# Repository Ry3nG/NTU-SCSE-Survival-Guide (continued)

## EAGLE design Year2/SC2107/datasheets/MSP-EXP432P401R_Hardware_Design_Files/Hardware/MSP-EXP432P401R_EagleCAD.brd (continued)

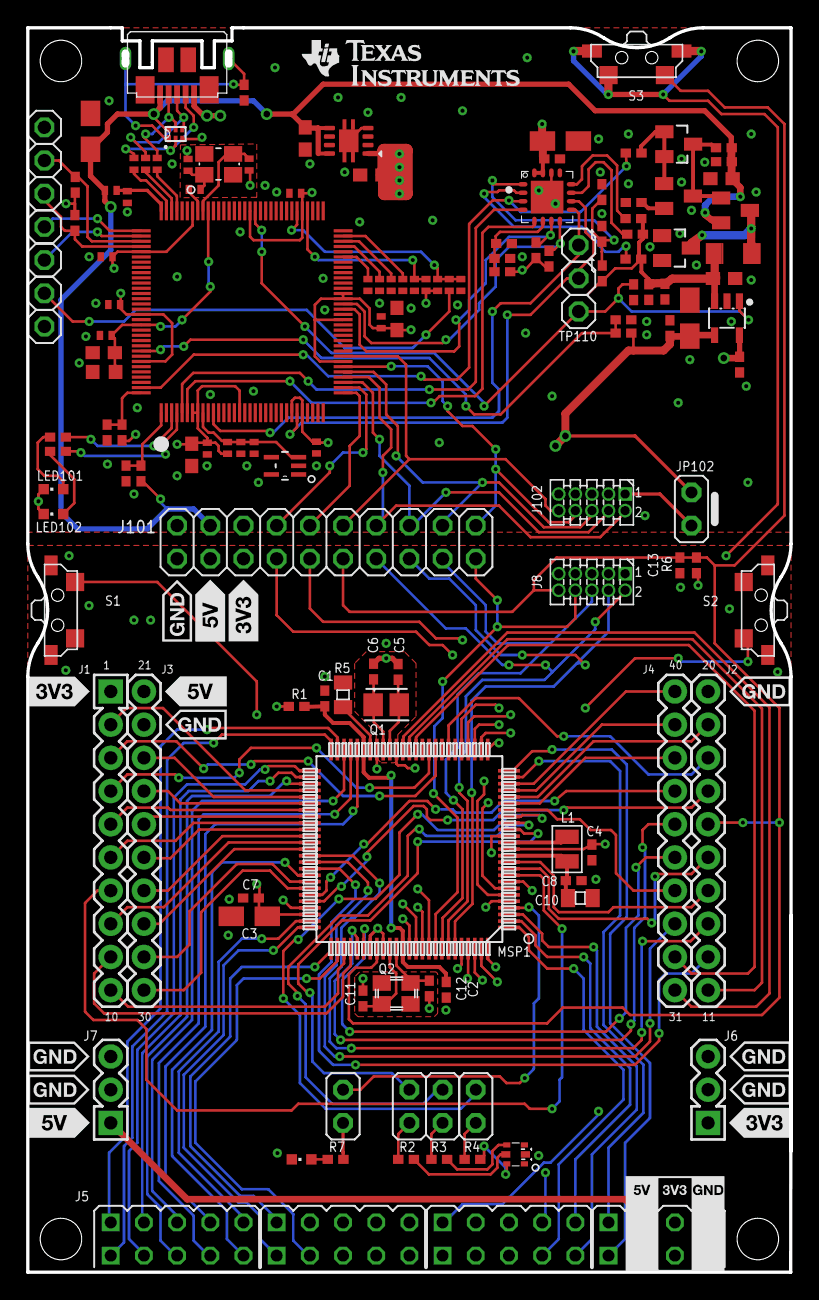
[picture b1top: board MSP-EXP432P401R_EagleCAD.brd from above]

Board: 4 copper layers, 58.1 x 94.9 mm, 149 parts (0 on the bottom side), 160 nets.

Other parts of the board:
DRAW3: LOGO-ROCKET-10X7MM-BRD
U$4: LOGO16_TPLACE

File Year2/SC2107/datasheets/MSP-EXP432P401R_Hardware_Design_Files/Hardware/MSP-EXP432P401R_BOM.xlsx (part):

BOM for MSP-EXP432P401R
Do not populate (Dnp) part if Quantity equals zero
Use exact PartNumber and Manufacturer if this data is provided
Feedback from CM needed where supplier equals CM
 | Qty | Reference | Manufacturer | Description | Part Number | PCB Decal/Package | Value | Supplier1 | Supplier Part Number | Comment
 | 1 | C1 | Standard | CAP CER 0.1UF 10V 20% X5R 0402,Digikey 445-4984-1-ND |  | 402 | 100n | Digikey | 445-4984-1-ND
 | 1 | C2 | Standard | CAP CER 0.1UF 10V 20% X5R 0402,Digikey 445-4984-1-ND |  | 402 | 100n | Digikey | 445-4984-1-ND
 | 1 | C3 | Standard | CAP TANT 10UF 10V 20% 1206,Digikey 493-2351-1-ND |  | TANT_3216 | 10u | Digikey | 493-2351-1-ND
 | 1 | C4 | Standard | CAP CER 0.1UF 10V 20% X5R 0402,Digikey 445-4984-1-ND |  | 402 | 100n | Digikey | 445-4984-1-ND
 | 1 | C5 | Standard | CAP CER 22PF 50V 5% NP0 0402, Digikey 445-1239-1-ND |  | 402 | 22p | Digikey | 445-1239-1-ND
 | 1 | C6 | Standard | CAP CER 22PF 50V 5% NP0 0402, Digikey 445-1239-1-ND |  | 402 | 22p | Digikey | 445-1239-1-ND
 | 1 | C7 | Standard | CAP CER 0.1UF 10V 20% X5R 0402,Digikey 445-4984-1-ND |  | 402 | 100n | Digikey | 445-4984-1-ND
 | 1 | C8 | Standard | CAP CER 0.1UF 10V 20% X5R 0402,Digikey 445-4984-1-ND |  | 402 | 100n | Digikey | 445-4984-1-ND
 | 1 | C10 | Standard | CAP CER 4.7UF 10V Y5V 0805, Digikey 445-1370-1-ND |  | 805 | 4.7u | Digikey | 445-1370-1-ND
 | 1 | C11 | Standard | CAP CER 22PF 50V 5% NP0 0402, Digikey 445-1239-1-ND |  | 402 | 22p | Digikey | 445-1239-1-ND
 | 1 | C12 | Standard | CAP CER 22PF 50V 5% NP0 0402, Digikey 445-1239-1-ND |  | 402 | 22p | Digikey | 445-1239-1-ND
 | 1 | C13 | Standard | CAP CER 1000PF 50V 10% X7R 0402,Digikey 445-1256-1-ND |  | 402 | 1n | Digikey | 445-1256-1-ND
 | 1 | C101 | Standard | CAP CER 12PF 50V 5% NP0 0402,Digikey 445-1236-1-ND |  | 402 | 12p | Digikey | 445-1236-1-ND
 | 1 | C102 | Standard | CAP CER 12PF 50V 5% NP0 0402,Digikey 445-1236-1-ND |  | 402 | 12p | Digikey | 445-1236-1-ND
 | 1 | C103 | Standard | CAP CER 0.1UF 10V 20% X5R 0402,Digikey 445-4984-1-ND |  | 402 | 100n | Digikey | 445-4984-1-ND
 | 1 | C104 | Standard | CAP CER 10000PF 10V 10% X7R 0402, Digikey 478-7890-1-ND |  | 402 | 10n | Digikey | 478-7890-1-ND
 | 1 | C105 | Standard | CAP CER 2.2UF 10V 10% X5R 0603, Digikey 587-1253-1-ND |  | 603 | 2.2u | Digikey | 587-1253-1-ND
 | 1 | C106 | Standard | CAP TANT 4.7UF 10V 10% 1206,Digikey 478-8221-1-ND |  | TANT_3216 | 4.7u | Digikey | 478-8221-1-ND
 | 1 | C107 | Standard | CAP CER 1UF 10V 10% X5R 0603, Digikey 445-1321-1-ND |  | 603 | 1u | Digikey | 445-1321-1-ND
 | 0 | C108 | Standard |  |  | 402 | dnp
 | 1 | C110 | Standard | CAP CER 10000PF 10V 10% X7R 0402, Digikey 478-7890-1-ND |  | 402 | 10n | Digikey | 478-7890-1-ND
 | 1 | C111 | Standard | CAP CER 0.1UF 10V 20% X5R 0402,Digikey 445-4984-1-ND |  | 402 | 100n | Digikey | 445-4984-1-ND
 | 1 | C112 | Standard | CAP CER 10000PF 10V 10% X7R 0402, Digikey 478-7890-1-ND |  | 402 | 10n | Digikey | 478-7890-1-ND
 | 1 | C113 | Standard | CAP CER 0.1UF 10V 20% X5R 0402,Digikey 445-4984-1-ND |  | 402 | 100n | Digikey | 445-4984-1-ND
 | 1 | C114 | Standard | CAP CER 10000PF 10V 10% X7R 0402, Digikey 478-7890-1-ND |  | 402 | 10n | Digikey | 478-7890-1-ND
 | 1 | C115 | Standard | CAP CER 33PF 50V 5% NP0 0402,Digikey 445-1241-1-ND |  | 402 | 33p | Digikey | 445-1241-1-ND
 | 1 | C116 | Standard | CAP CER 33PF 50V 5% NP0 0402,Digikey 445-1241-1-ND |  | 402 | 33p | Digikey | 445-1241-1-ND
 | 1 | C117 | Standard | CAP CER 4.7UF 10V 10% X5R 0603,Digikey 445-5170-1-ND |  | 603 | 4.7u | Digikey | 445-5170-1-ND
 | 1 | C118 | Standard | CAP CER 0.1UF 10V 20% X5R 0402,Digikey 445-4984-1-ND |  | 402 | 100n | Digikey | 445-4984-1-ND
 | 1 | C119 | TDK | CAP CER 4.7UF 10V 10% X5R 0603, Digikey 445-5170-1-ND | C1608X5R1A475K080AC | 603 | 4.7u | Digikey | 445-5170-1-ND
 | 1 | C120 | Standard | CAP CER 0.1UF 10V 20% X5R 0402,Digikey 445-4984-1-ND |  | 402 | 100n | Digikey | 445-4984-1-ND
 | 1 | C121 | Standard | CAP CER 0.1UF 10V 20% X5R 0402,Digikey 445-4984-1-ND |  | 402 | 100n | Digikey | 445-4984-1-ND
 | 1 | C123 | Standard | CAP CER 10000PF 10V 10% X7R 0402, Digikey 478-7890-1-ND |  | 402 | 10n | Digikey | 478-7890-1-ND
 | 1 | C124 | Standard | CAP CER 0.1UF 10V 20% X5R 0402,Digikey 445-4984-1-ND |  | 402 | 100n | Digikey | 445-4984-1-ND
 | 1 | C126 | Standard | CAP CER 0.22UF 16V 10% X5R 0402,Digikey 445-4972-1-ND |  | 402 | 220n | Digikey | 445-4972-1-ND
 | 1 | C127 | Standard | CAP CER 0.22UF 16V 10% X5R 0402,Digikey 445-4972-1-ND |  | 402 | 220n | Digikey | 445-4972-1-ND
 | 1 | C128 | Standard | CAP CER 47UF 10V 20% X5R 1206, Digikey 445-6006-1-ND |  | TANT_3216 | 47u | Digikey | 445-6006-1-ND
 | 1 | C129 | Standard | CAP CER 0.1UF 10V 20% X5R 0402,Digikey 445-4984-1-ND |  | 402 | 100n | Digikey | 445-4984-1-ND
 | 1 | C130 | Standard | CAP CER 1UF 10V 10% X5R 0603, Digikey 445-1321-1-ND |  | 603 | 1u | Digikey | 445-1321-1-ND
 | 1 | C131 | Standard | CAP CER 0.1UF 10V 20% X5R 0402,Digikey 445-4984-1-ND |  | 402 | 100n | Digikey | 445-4984-1-ND
 | 1 | C132 | Standard | CAP CER 1UF 10V 10% X5R 0603, Digikey 445-1321-1-ND |  | 603 | 1u | Digikey | 445-1321-1-ND
 | 1 | C133 | Standard | CAP CER 2.2UF 10V 10% X5R 0603, Digikey 587-1253-1-ND |  | 603 | 2.2u | Digikey | 587-1253-1-ND
 | 1 | C140 | Standard | CAP TANT 4.7UF 10V 10% 1206,Digikey 478-8221-1-ND |  | TANT_3216 | 4.7u | Digikey | 478-8221-1-ND
 | 1 | C141 | Standard | CAP CER 1UF 10V 10% X5R 0603, Digikey 445-1321-1-ND |  | 603 | 1u | Digikey | 445-1321-1-ND
 | 1 | C150 | Standard | CAP CER 0.1UF 10V 20% X5R 0402,Digikey 445-4984-1-ND |  | 402 | 100n | Digikey | 445-4984-1-ND
 | 1 | D101 | NXP | DIODE SCHOTTKY 40V 120MA TO236AB,Digikey 568-4862-1-ND | BAS40-05 215 | SOT-23 | BAS40-05 | Digikey | 568-4862-1-ND
 | 1 | D102 | NXP | DIODE SCHOTTKY 40V 120MA TO236AB,Digikey 568-4862-1-ND | BAS40-05 215 | SOT-23 | BAS40-05 | Digikey | 568-4862-1-ND
 | 1 | IC101 | TI | IC REG LDO 3.3V 0.5A 8SON,Digikey 296-24854-1-ND | TPS73533DRB |  | TPS73533DRB | Digikey | 296-24854-1-ND
 | 1 | IC102 | TI | IC 4CH ESD-PROT ARRAY 6-SON,Digikey 296-23618-1-ND | TPD4E004DRY | USON | TPD4E004DRY | Digikey | 296-23618-1-ND
 | 1 | IC103 | TI | IC OR CTRLR SRC SELECT SOT23-5, Digikey 296-10880-1-ND | TPS2012DBV | SOT23-5 | TPS2012DBV | Digikey | 296-10880-1-ND
 | 1 | IC106 | TI | IC MCU 32BIT | TM4C1294NCPDT |  | TM4C1294NCPDT | Digikey | 296-38028-ND
 | 1 | IC107 | TI | IC VREF SHUNT PREC 2.5V SC-70-5, Digikey 296-20873-1-ND | LM4040B25DCK | SC70-5 | LM4040B25DCK | Digikey | 296-20873-1-ND
 | 1 | J1/J3 | CM | CONN HEADER 20POS .100" DUAL, FEMALE with long male leads | CNT-F254-2*10-GS-850-9 | 2X10 |  | CM | to be provided by CM
 | 1 | J2/J4 | CM | CONN HEADER 20POS .100" DUAL, FEMALE with long male leads | CNT-F254-2*10-GS-850-9 | 2X10 |  | CM | to be provided by CM
 | 0 | J5 | Standard | CONN HEADER .100 DUAL STR 40POS,Digikey S2012E-20-ND |  | 0.100 inch x 2 x 20 | dnp | Digikey | S2012E-20-ND
 | 1 | J6 | Standard | CONN HEADER .100 SINGL STR 3POS,Digikey S1012E-03-ND |  | 0.100 inch x 3 |  | Digikey | S1012E-03-ND
 | 1 | J7 | Standard | CONN HEADER .100 SINGL STR 3POS,Digikey S1012E-03-ND |  | 0.100 inch x 3 |  | Digikey | S1012E-03-ND
 | 1 | J8 | Samtec | CONN HEADER 10POS DUAL VERT, Digikey FTSH-105-01-F-D-K-ND | FTSH-105-01-F-D-K |  |  | Digikey | FTSH-105-01-F-D-K-ND
 | 1 | JP8 | Standard | CONN HEADER .100 SINGL STR 2POS,Digikey S1012E-02-ND |  | 0.100 inch x 2 | Place Jumper | Digikey | S1012E-02-ND
 | 1 | JP9 | Standard | CONN HEADER .100 SINGL STR 2POS,Digikey S1012E-02-ND |  | 0.100 inch x 2 | Place Jumper | Digikey | S1012E-02-ND
 | 1 | JP10 | Standard | CONN HEADER .100 SINGL STR 2POS,Digikey S1012E-02-ND |  | 0.100 inch x 2 | Place Jumper | Digikey | S1012E-02-ND
 | 1 | JP11 | Standard | CONN HEADER .100 SINGL STR 2POS,Digikey S1012E-02-ND |  | 0.100 inch x 2 | Place Jumper | Digikey | S1012E-02-ND
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
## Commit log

2022-11-03 upload file
2022-11-03 managed directory
2022-11-03 uplaod readme
2022-11-03 uploaded readme
2022-11-03 upload readme
2022-11-04 upload
2023-01-31 Lab1
2023-04-27 uploaded 2103 lab codes
2023-04-27 uploaded sc2005 and sc2008 lab codes
2023-04-27 updated readme (MDP)
2024-02-15 uploaded 3102,3050, 3103 lab1
2024-04-02 removed lab5 code because this is an assessment
2024-04-03 upload lab 3 code
2024-04-03 upload lab4 code
